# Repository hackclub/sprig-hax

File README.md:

# This repository has been deprecated. All sprighax related stuff(s) can be found at https://github.com/Sheepy3/sprig/tree/main/sprig-hax

# SPRIGHAX

Hacking the sprig with experimental hardware and software features.

Sprighax #1. Custom board, UART, & Gyro 

*none of my fellows be hacking the sprig. it's time to start sprigmaxxing*

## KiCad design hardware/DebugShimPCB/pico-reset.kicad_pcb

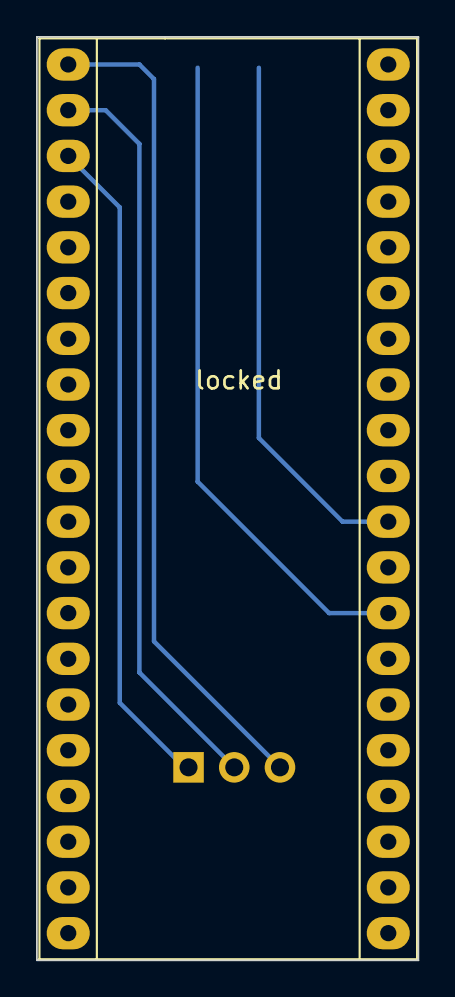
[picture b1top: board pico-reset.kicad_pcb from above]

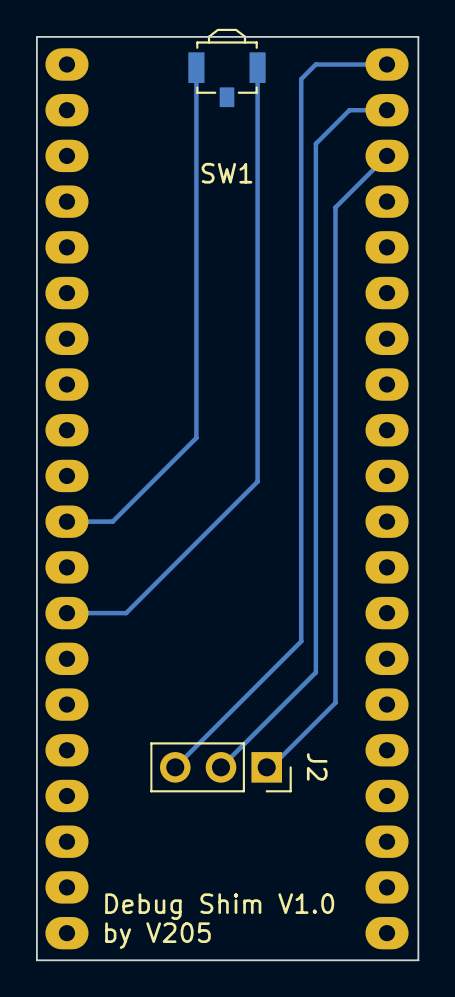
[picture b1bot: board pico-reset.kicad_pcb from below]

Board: 2 copper layers, 21.2 x 51.3 mm, 3 parts (2 on the bottom side), 5 nets.

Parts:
J2: PINHD_1x3_Female; PinSocket_1x03_P2.54mm_Vertical
SW1: Push_Button; SW_SPST_B3U-3100P
locked: locked; raspberry_pi_pico_THT

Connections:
GND: J2.1, locked.3 (GND)
unnamed: SW1.2, locked.28 (GND)
unnamed: J2.3, locked.1 (GP0)
unnamed: J2.2, locked.2 (GP1)
unnamed: SW1.1, locked.30 (RUN)

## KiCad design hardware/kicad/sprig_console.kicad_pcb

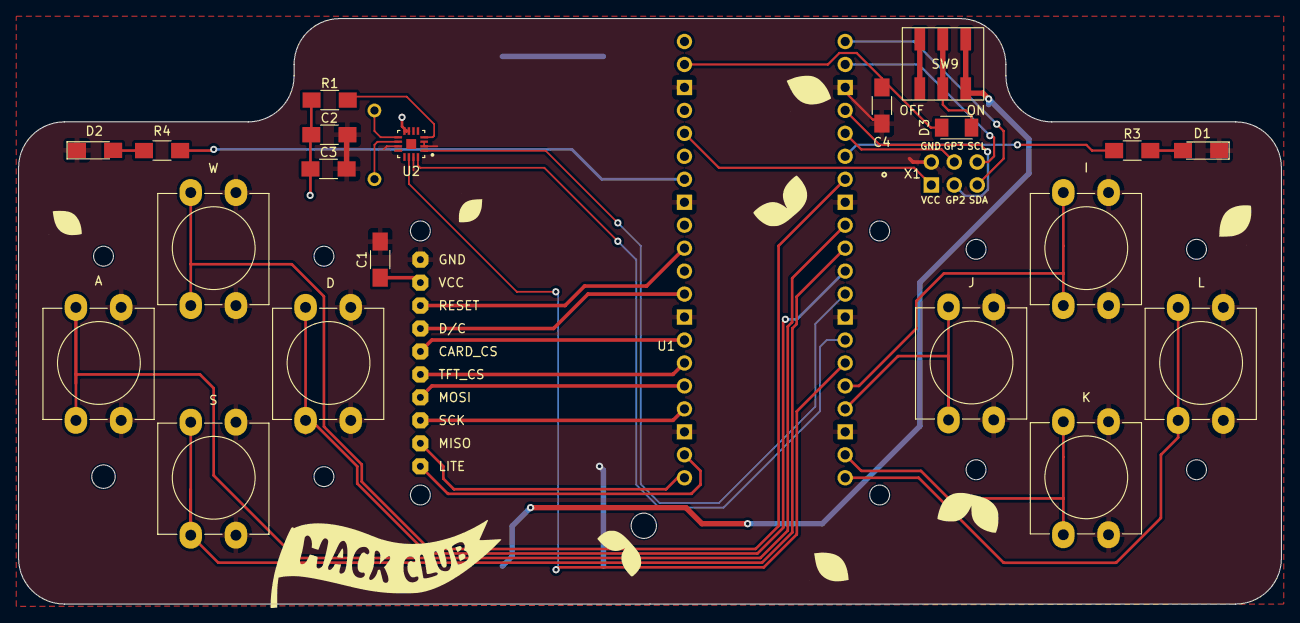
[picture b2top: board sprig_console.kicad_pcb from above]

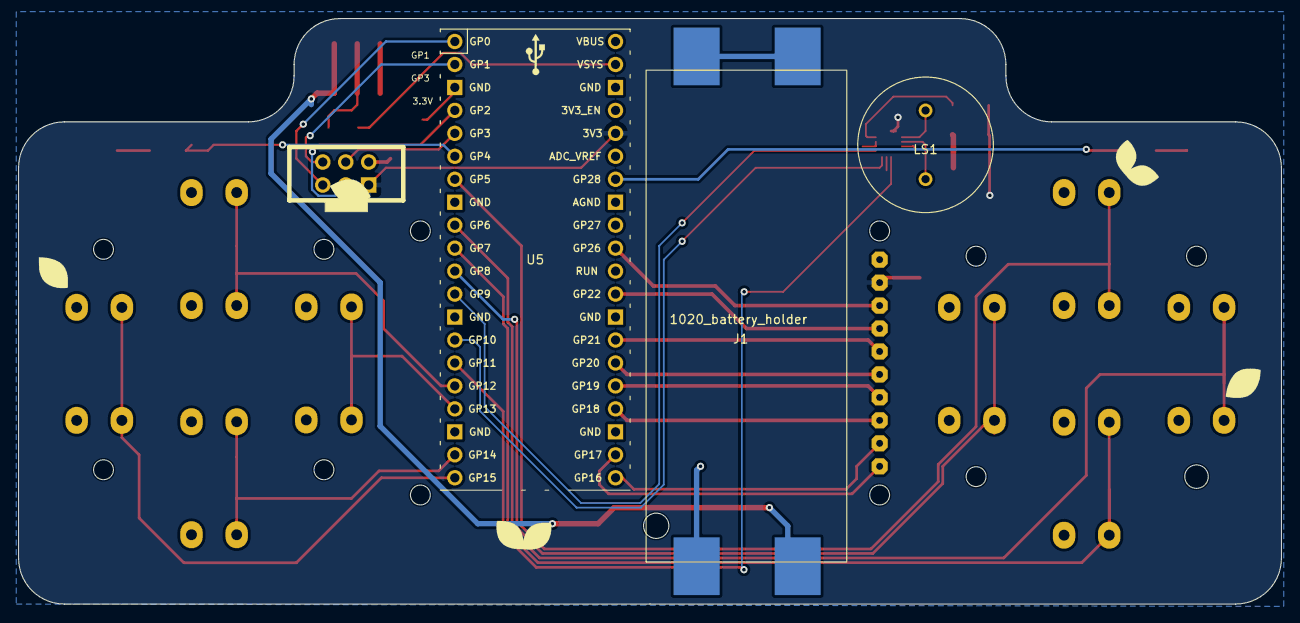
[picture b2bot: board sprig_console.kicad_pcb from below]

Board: 2 copper layers, 139.7 x 64.8 mm, 26 parts (5 on the bottom side), 36 nets.

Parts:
C1, C4: 1uF; C_1206
C2: 10uF; C_1206
C3: 0.1uF; C_1206
D1: R_LED; LED_1206
D2: L_LED; LED_1206
D3: SD1206T020S1R0; Diode_Schotky_100V_1A_Mini_SMA
J1: 1020_battery_holder; 1022
LS1: Speaker; CVS-1508
R1: 1M; R_1206
R3, R4: 1k; R_1206
Ref**: Val**; usb
SW1: W; SW_PUSH-12mm_Wuerth-430476085716
SW2: A; SW_PUSH-12mm_Wuerth-430476085716
SW3: S; SW_PUSH-12mm_Wuerth-430476085716
SW4: D; SW_PUSH-12mm_Wuerth-430476085716
SW5: I; SW_PUSH-12mm_Wuerth-430476085716
SW6: J; SW_PUSH-12mm_Wuerth-430476085716
SW7: K; SW_PUSH-12mm_Wuerth-430476085716
SW8: L; SW_PUSH-12mm_Wuerth-430476085716
SW9: Slideswitch; slideswitchCK
U1: Adafruit_TFT_ST7735; TFT_ST7735
U2: MAX98357AETE+; QFN50P300X300X80-17N
U5: Pico; RPi_Pico_SMD_TH_mod
X1: Simple_Addon_v2; Simple_Addon_v2-BADGE-2x3

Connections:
+3V3: C1.1, C2.1, C3.1, R1.1, U1.9 (VCC), U2.7 (VDD), U2.8 (VDD), U5.36 (3V3), X1.1 (VCC)
BCLK: U2.16 (BCLK), U5.14 (GPIO10)
BTN_A: SW2.1, U5.9 (GPIO6)
BTN_D: SW4.1, U5.11 (GPIO8)
BTN_I: SW5.1, U5.16 (GPIO12)
BTN_J: SW6.1, U5.17 (GPIO13)
BTN_K: SW7.1, U5.19 (GPIO14)
BTN_L: SW8.1, U5.20 (GPIO15)
BTN_S: SW3.1, U5.10 (GPIO7)
BTN_W: SW1.1, U5.7 (GPIO5)
CARD_CS: U1.6 (CARD_CS), U5.27 (GPIO21)
DIN: U2.1 (DIN), U5.12 (GPIO9)
D/C: U1.7 (D/C), U5.29 (GPIO22)
GND: C1.2, C2.2, C3.2, C4.2, D1.1 (K), D2.1 (K), J1.1, SW1.2, SW2.2, SW3.2, SW4.2, SW5.2, SW6.2, SW7.2, SW8.2, U1.10 (GND), U2.2 (GAIN_SLOT), U2.3 (GND), U2.11 (GND), U2.15 (GND), U5.3 (GND), U5.8 (GND), U5.13 (GND), U5.18 (GND), U5.23 (GND), U5.28 (GND), U5.33 (AGND), U5.38 (GND), X1.2 (GND)
GPIO0: U5.1 (GPIO0), X1.5 (GPIO1)
GPIO1: U5.2 (GPIO1), X1.6 (GPIO2)
GPIO2: U5.4 (GPIO2), X1.3 (SDA)
GPIO3: U5.5 (GPIO3), X1.4 (SCL)
LED_L: R4.1, U5.34 (GPIO28_ADC2)
LED_R: R3.1, U5.6 (GPIO4)
LITE: U1.1 (LITE), U5.22 (GPIO17)
LRCLK: U2.14 (LRCLK), U5.15 (GPIO11)
MISO: U1.2 (MISO), U5.21 (GPIO16)
MOSI: U1.4 (MOSI), U5.25 (GPIO19)
unnamed: D1.2 (A), R3.2
unnamed: D2.2 (A), R4.2
unnamed: D3.2 (A), SW9.2 (B)
unnamed: C4.1, D3.1 (K), U5.39 (VSYS)
unnamed: J1.2, J1.3
unnamed: J1.4, SW9.3 (C)
unnamed: LS1.1, U2.10 (OUTN)
unnamed: LS1.2, U2.9 (OUTP)
unnamed: R1.2, U2.4 (~SD_MODE)
RESET: U1.8 (RESET), U5.31 (GPIO26_ADC0)
SCK: U1.3 (SCK), U5.24 (GPIO18)
TFT_CS: U1.5 (TFT_CS), U5.26 (GPIO20)

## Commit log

2024-02-09 updated PCB
2024-02-09 flipped connector to face other side
2024-02-12 updated board design (moved SAO connector)
2024-02-12 Create README.md
    extremely useful readme
2024-02-15 reorganize repo
2024-02-15 Rename sprig_gyro.md to README.md
2024-02-16 Reorganize hardware directories
2024-02-17 add files, hope I did it right
2024-02-18 change hole sizing
    just made pad drill holes 0.1mm smaller.
2024-02-18 reorganize hardware
2024-02-18 generate gerbers, add credit
2024-02-18 update hole size (again..)
    update holes on shim to be tighter fit to headers.
2024-02-28 added conclusion and gamefile
2024-02-29 updated gyro
